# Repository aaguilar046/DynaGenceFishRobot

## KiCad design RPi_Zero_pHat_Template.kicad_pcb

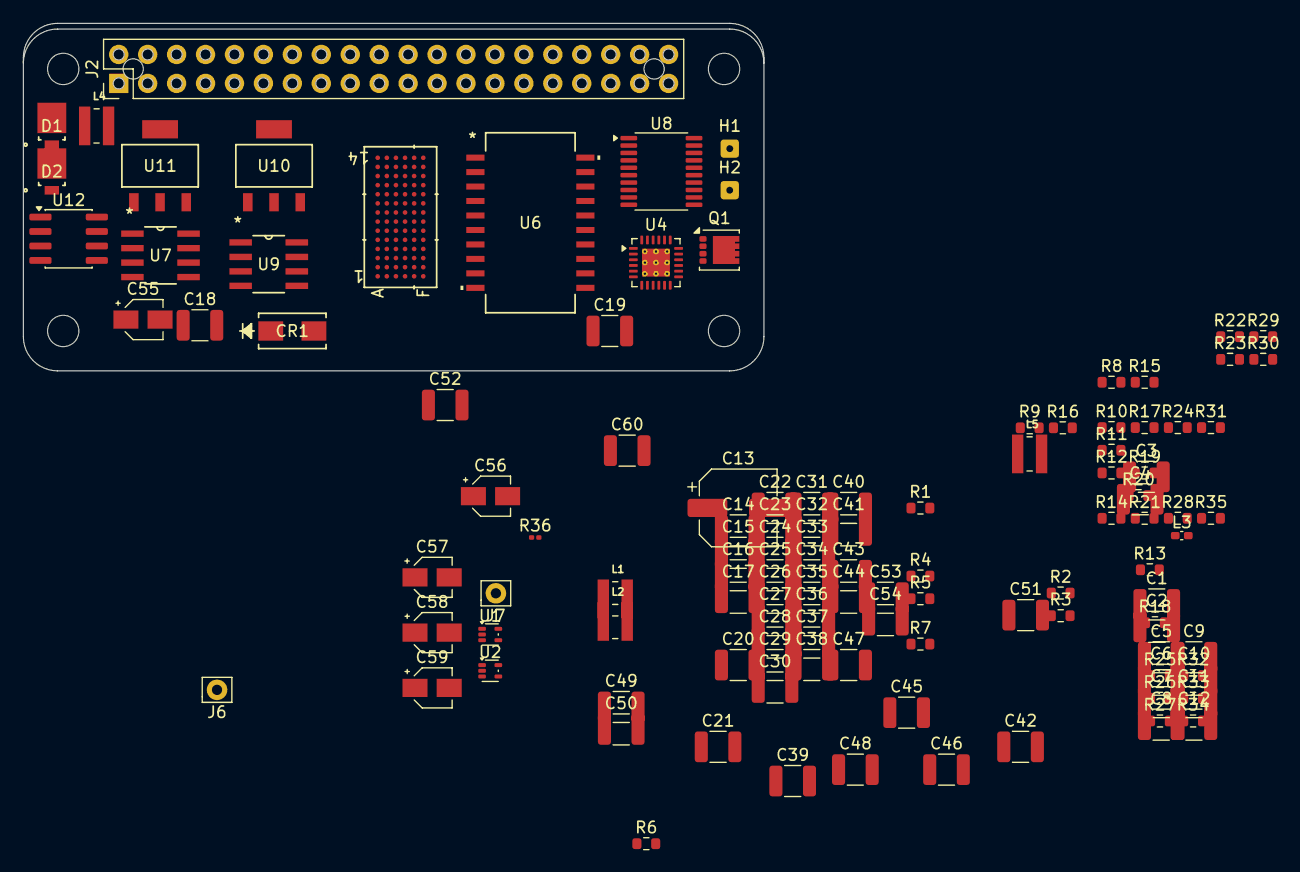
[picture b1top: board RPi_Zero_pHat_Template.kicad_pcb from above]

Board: 2 copper layers, 65.0 x 30.5 mm, 122 parts (1 on the bottom side), 66 nets, no tracks yet.

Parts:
C1, C4, C6, C9: 22uF; C_1210_3225Metric
C2, C5, C7, C10, C30: 100nF; C_1210_3225Metric
C3, C8: 10pF; C_1210_3225Metric
C11, C18: 1uF; C_1210_3225Metric
C12, C19, C25, C27, C28, C29: C; C_1210_3225Metric
C13: 22uF; CP_Elec_6.3x5.8
C14, C31, C32: 4.7uF; C_1210_3225Metric
C15: 6.8nF; C_1210_3225Metric
C16: 390pF; C_1210_3225Metric
C17: 47uF; C_1210_3225Metric
C20: 33nF; C_1210_3225Metric
C21, C22, C48, C49: 1nf; C_1210_3225Metric
C23, C50: 2.7nF; C_1210_3225Metric
C24, C26: 1pf; C_1210_3225Metric
C33: 10nF; C_1210_3225Metric
C34: 4.7nF; C_1210_3225Metric
C35: set 5; C_1210_3225Metric
C36: set 10; C_1210_3225Metric
C37: set 9; C_1210_3225Metric
C38: set 4; C_1210_3225Metric
C39, C41, C45: 0.1uF; C_1210_3225Metric
C40, C42, C46: 10uF; C_1210_3225Metric
C43, C44: 2.2uF; C_1210_3225Metric
C47: 2.2nF; C_1210_3225Metric
C51, C53: 0.47uF; C_1210_3225Metric
C52, C54: 33uF; C_1210_3225Metric
C55, C57: 1uF; CP_Elec_3x5.3
C56: 2.2uF; CP_Elec_3x5.3
C58: See Note; CP_Elec_3x5.3
C59: See note; CP_Elec_3x5.3
C60: 220nF; C_1210_3225Metric
CR1: SK220ATR; DIODE_SK220ATR_SMC
D1, D2: MBRM120ET1G; DO-216AA_ONS
H1: TransducerRX; SolderWire-0.1sqmm_1x01_D0.4mm_OD1mm
H2: Transducer RX; SolderWire-0.1sqmm_1x01_D0.4mm_OD1mm
J1: RPi_GPIO; Samtec_HLE-120-02-xxx-DV-BE-A_2x20_RPi_Bottom
J2: RPi_GPIO; PinHeader_2x20_P2.54mm_Vertical
J6: Conn_01x06_Pin; Pin_D0.9mm_L10.0mm_W2.4mm_FlatFork
J7: Conn_01x04_Pin; Pin_D0.9mm_L10.0mm_W2.4mm_FlatFork
L1, L2, L4: 4.7uH; IND_VLS3012HBX-4R7M
L3: 10uH; L_0402_1005Metric_Pad0.77x0.64mm_HandSolder
L5: 4.7 uH; IND_VLS3012HBX-4R7M
Q1: CSD18543Q3A; VSON-8_3.3x3.3mm_P0.65mm_NexFET
R1, R6: 113k; R_0603_1608Metric
R2, R4, R7, R10: 30k; R_0603_1608Metric
R3: 220k; R_0603_1608Metric
R5, R8, R30, R31: 10k; R_0603_1608Metric
R9: 237k; R_0603_1608Metric
R11: 19.1Ohm; R_0603_1608Metric
R12: 1k; R_0603_1608Metric
R13: 12M; R_0603_1608Metric
R14: 56k; R_0603_1608Metric
R15: 487; R_0603_1608Metric
R16: 28.7k; R_0603_1608Metric
R17: 309k; R_0603_1608Metric
R18, R19: 348ohm; R_0603_1608Metric
R20, R21: 7150ohm; R_0603_1608Metric
R22, R23, R34, R35: 40; R_0603_1608Metric
R24: 100 Ohm; R_0603_1608Metric
R25: set 3; R_0603_1608Metric
R26: set 4; R_0603_1608Metric
R27: set 2; R_0603_1608Metric
R28: set; R_0603_1608Metric
R29: 470; R_0603_1608Metric
R32, R33: 270ohm; R_0603_1608Metric
R36: 11; R_0201_0603Metric
U1, U2: TPS564257DRLR; SOT-553
U4: TPS65131RGE; VQFN-24-1EP_4x4mm_P0.5mm_EP2.45x2.45mm_ThermalVias
U5: ADAQ7767-1BBCZ; BC-84-4_ADI
U6: ADUM4150ARIZ-RL; RI-20-1_ADI
U7, U9: OPA1632DR; D8
U8: PCM5102A; TSSOP-20_4.4x6.5mm_P0.65mm
U10, U11: LM3940IMPX-3.3/NOPB; MP04A
U12: ADR4540; SOIC-8_3.9x4.9mm_P1.27mm

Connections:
/3.3V: C24.1, C27.2, C41.2, C42.2, J6.1 (Pin_1_1), U5.C10 (PIN/SPI), U5.E14 (VDD_IO), U6.1 (VDD1), U8.20 (DVDD)
/3.3VA: C45.2, C46.2, C54.1, U8.1 (CPVDD), U11.3 (OUT)
/3.3VD: C52.1, U8.8 (AVDD), U10.3 (OUT)
/5.3Vout: C8.1, C9.1, C10.1, C25.1, L2.2, R8.2, R9.1, U5.C5 (IN_LDO), U5.C6 (IN_LDO), U5.C7 (IN_LDO), U5.D14 (EN_LDO)
/5Vout: C3.1, C4.1, C5.1, C26.1, C31.1, C32.1, C51.1, C53.1, L1.2, L4.1, R3.1, R5.2, R24.1, U4.5 (INN), U4.6 (INN), U6.20 (VDD2), U10.1 (IN), U11.1 (IN)
/15Vout: C37.1, C38.1, D1.1 (K), R28.1, U4.23 (VPOS), U7.3 (V+), U9.3 (V+)
/30Vout: C13.1, C14.1, CR1.1, R14.1
/-15Vout: C35.1, C36.2, D2.2 (A), R25.2, U4.15 (VNEG), U7.6 (V-), U9.6 (V-)
/AGND: C26.2, U5.F4 (AGND), U6.19 (GND2)
/BattIn: C1.2, C2.1, C6.2, C7.1, C17.1, C18.1, L3.1, R1.1, R6.1, R17.2, U1.1 (VIN), U2.1 (VIN)
/Dout/RDY: U5.C11 (DOUT/RDY), U6.16 (SO)
/Out_LDO: C57.1, U5.B2 (VDD_ADC), U5.B4 (VDD_ADC), U5.B5 (VDD2_ADC), U5.B12 (VDD_FDA), U5.B13 (VDD_FDA), U5.B14 (VDD_FDA), U5.E11 (OUT_LDO), U5.E12 (OUT_LDO), U5.E13 (OUT_LDO), U12.2 (IN)
/RCLO: C47.1, R29.2, R30.1
/SCLK: U5.C12 (SCLK), U6.18 (SCLK)
/SigPlus: C23.2, R20.2, R23.1, U5.C1 (IN2+)
/SigToSlave: U5.C13 (SDI), U6.17 (SI)
/Sigminus: C23.1, R21.2, R22.2, U5.C4 (IN2-)
GND: C1.1, C2.2, C4.2, C5.2, C6.1, C7.2, C9.2, C10.2, C11.2, C12.2, C13.2, C14.2, C17.2, C18.2, C19.2, C20.2, C25.2, C27.1, C28.1, C29.1, C30.1, C31.2, C32.2, C33.2, C34.2, C35.2, C38.2, C39.2, C40.2, C41.1, C42.1, C44.2, C45.1, C46.1, C47.2, C51.2, C52.2, C53.2, C54.2, C55.2, C56.2, C57.2, C58.2, C59.2, C60.2, L5.2, R2.2, R4.2, R7.2, R10.2, R13.2, R15.2, R27.2, R31.2, U1.3 (GND), U2.3 (GND), U4.2 (PGND), U4.3 (PGND), U4.19 (AGND), U5.C9 (REF-), U5.E10 (CLK_SEL), U5.F1 (AGND), U6.5 (MI), U7.2 (VOCM), U8.3 (CPGND), U8.9 (AGND), U8.10 (DEMP), U8.11 (FLT), U8.12 (SCK), U8.16 (FMT), U8.19 (DGND), U9.2 (VOCM), U10.2 (GND), U11.2 (GND), U12.4 (GND)
unnamed: C15.2, R16.1
unnamed: C24.2, U6.2 (GND1)
unnamed: C50.1, R33.2, R34.2
unnamed: C50.2, R32.2, R35.1
unnamed: D1.2 (A), L4.2, U4.1 (INP), U4.24 (INP)
unnamed: D2.1 (K), L5.1, U4.13 (OUTN), U4.14 (OUTN)
unnamed: CR1.2, L3.2, Q1.5 (D)
unnamed: Q1.4 (G), R11.2
unnamed: Q1.1 (S), Q1.2 (S), Q1.3 (S), R12.2, R13.1
unnamed: R25.1, R26.2
unnamed: R1.2, R2.1, U1.5 (EN)
unnamed: C3.2, R3.2, R4.1
unnamed: R5.1, U1.4 (PG)
unnamed: L1.1, U1.2 (SW)
unnamed: R6.2, R7.1, U2.5 (EN)
unnamed: C8.2, R9.2, R10.1
unnamed: R8.1, U2.4 (PG)
unnamed: L2.1, U2.2 (SW)
unnamed: C15.1, C16.1
unnamed: C16.2, R14.2, R15.1, R16.2
unnamed: C12.1, R12.1
unnamed: C19.1, R17.1
unnamed: C34.1, U4.18 (CN)
unnamed: C33.1, U4.21 (CP)
unnamed: C30.2, R24.2, U4.4 (VIN), U4.8 (ENP), U4.9 (PSP), U4.10 (ENN), U4.11 (PSN)
unnamed: C36.1, U4.16 (FBN)
unnamed: C37.2, R27.1, R28.2, U4.22 (FBP)
unnamed: C60.1, R26.1, U4.17 (VREF)
unnamed: C28.2, U5.A11 (AREG_CAP)
unnamed: U5.C14 (CS), U6.15 (*SSS)
unnamed: C29.2, U5.F11 (DGND), U5.F12 (DREG_CAP)
unnamed: C56.1, R36.2, U5.D1 (REF+)
unnamed: C59.1, U5.F13 (XTAL1)
unnamed: C58.1, U5.F14 (XTAL2_MCLK)
unnamed: C21.1, R18.2, R21.1, U7.8 (VIN+)
unnamed: C22.1, R19.1, R20.1, U7.1 (VIN-)
unnamed: C21.2, R22.1, U7.4 (VOUT+)
unnamed: C22.2, R23.2, U7.5 (VOUT-)
unnamed: C43.2, U8.4 (CAPM)
unnamed: C43.1, U8.2 (CAPP)
unnamed: C39.1, C40.1, U8.18 (LDOO)
unnamed: R29.1, U8.7 (OUTR)
unnamed: C44.1, U8.5 (VNEG)
unnamed: C48.1, R30.2, R33.1, U9.8 (VIN+)
unnamed: C49.1, R31.1, R32.1, U9.1 (VIN-)
unnamed: C48.2, R34.1, U9.4 (VOUT+)
unnamed: C49.2, R35.2, U9.5 (VOUT-)
unnamed: C55.1, R36.1, U12.6 (OUT)
